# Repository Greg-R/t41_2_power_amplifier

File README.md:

# T41-2 Power Amplifier Version 1.7

This is the PCB for the Power Amplifier for the T41 "Software Defined Transceiver".
This PCB was designed using the open-source design tool Kicad 9.0.

The Power Amplifier is designed to driven by the T41-2 Low Power Amplifier, described here:

<https://github.com/Greg-R/t41_2_low_power_amplifier>

The Low Power Amplifier combined with the Power Amplifier are intended to replace the
original V11 Power Amplifier which uses IRF510 switching MOSFETs in the final amplifier
stage.  This new design will improve all aspects of power amplifier performance, 
including linearity, power, efficiency, and bandwidth.  An important difference is that
the amplifier operates from a 13.8 volt supply.  No "boost" module is required.

The schematic is here:

<https://github.com/Greg-R/t41_2_power_amplifier/blob/main/doc/t41_2_power_amplifier.pdf>

# Licensing

Please note the included license files.  The software license, GNU GENERAL PUBLIC LICENSE
Version 3, covers the design files.
The hardware license, CERN Open Hardware Licence Version 2 - Strongly Reciprocal, covers
the PCB and circuitry.

# Design Details

## Amplifier Design Notes 

The Power Amplifier is a conventional push-pull circuit using Mitsubishi RD16HHF1 devices.

The input network is an impedance matching transformer with a center-tapped secondary.
A resistive network is used for DC gate bias of the MOSFETS as well as for stability.
The two MOSFETs have independent bias adjustments due to the wide threshold voltage
variation of MOSFET devices.

A bifilar wound inductor provides DC bias to the MOSFET drains.

Each MOSFET has a transformer wound on a binocular core.  These are combined in parallel
on the output.  This results in a compact layout while preserving good bandwidth.

## DC Biasing and Thermal Protection Circuits 

A 10 volt regulator provides the bias voltage to the potentiometers which are used to set
the MOSFET quiescent bias currents.

There is also an optional "thermostat" device which shuts down the amplifier if the
temperature rises above a threshold set by a resistor value.  The thermostat is
positioned in close proximity to the output amplifier devices.  Experiments are
ongoing with this device to determine what temperature setting should be used.

Please note the electrolytic capacitors on the 13.8 volt supply net.  These are not
required in the case of a 13.8 volt supply voltage.  The 10uF ceramic capacitors, rated at
25 volts, are used in this case.  If it is desired to operate at a higher voltage, the
ceramics must be replaced with higher voltage electrolytics (not tested yet).

## Bill of Material

The Digikey BOM is here:

<https://www.digikey.com/en/mylists/list/1GX6JR00JS>

Four ferrite cores are required:

Quantity 2 BN-43-302 binocular cores.
Quantity 2 BN-43-202 binocular cores.

You will also need a small quantity of #24, #26, and #22 magnet wire.  I order this
on spools from Amazon:

<https://www.amazon.com/dp/B07DYF89T9?th=1>

I ordered the cores from:

<https://kitsandparts.com>

Also some hardware is required.  I used this outstanding heatsink:

<https://www.amazon.com/dp/B07TJY3GKP?th=1>

Some sort of stand-offs or spacers are required to hold the PCB above the heatsink.
These 5mm spacers are perfect:

<https://www.amazon.com/dp/B0CQ3TKVBD?th=1>

I use this type of caphead bolt to secure the PCB to the heatsink:

<https://www.amazon.com/dp/B0DYMYHHWH?th=1>

Two 3mm bolts and washers are required to bolt down the final amplifier devices.
A small amount of heatsink compound under the devices is recommended.

A 5 amp bladed style automotive fuse is required.

# Build Instructions

The Power Amplifier build is similar to the other boards in the T41-2 series,
with the exception being the ferrite cores which must be constructed with great
care.  I am going to create another document to cover the construction of the
three ferrite devices (T1, L2, T2 and T3).

The installation of the final amplifier devices Q1 and Q3 will be covered in
the same document as the ferrites.

The board has components on both sides.  I recommend using a hot plate for the
top side components.  Use a hot air gun for the bottom side components.

# Tune Up

## DC Bias Adjustment

There is an DC bias current adjustment for the two final amplifier MOSFETs.
The potentiometers are R17 and R11. 

It is important to set the potentiometers for minimal bias current before applying
power!!!  If the potentiometer is oriented as in the photograph (below) the 
potentiometer should be rotated counterclockwise until up against the stop.
Make sure both are set against the stop before proceeding with bias adjustment.

Since this is a Class-AB amplifier, the bias point should be set for optimal
linearity at the lowest current possible.

There is a trade-off here between linearity and efficiency.  The recommended
bias current was determined emperically.  However, if you want more efficiency,
and you are a CW operator only, decrease the bias current.  If you want even
more linearity for SSB operation, increase the bias current, with the 
trade-off being less amplifier efficiency.
 
The 13.8 volt current should be set for approximately 500 milliamperes per device
with no RF drive.  Slowly rotate one of the potentiometers clockwise until this current
is achieved.  The current may drift a few milliamperes as the devices warm up.
This is normal, and the exact bias current setting is not critical. Continue
with the second potentiometer until the total bias current is 1.0 amps. 

## Linearity Testing

The T41EEE firmware includes a "two-tone" test which can be used to evaluate the
linearity of a power amplifier.

# High Resolution Photos

The top side of the completed board:

<https://drive.google.com/file/d/1ic4hn-198JwR1nAGYp5Wp3Prv69H474b/view?usp=drive_link>

Side view of the completed module, showing the heatsink, TO-220 devices, and spacers:

<https://drive.google.com/file/d/1cEXMb9Utur-sG8AnGmGLAzppEAz-hgnM/view?usp=drive_link>

End view of the Power Amplifier, showing the spacers and heatsink:

<https://drive.google.com/file/d/1fRfvSwTNmH1s3oaT6EwBXt0dI4ggvO0P/view?usp=drive_link>

# Mounting the Power Amplifier to the T41 Radio

By drilling and tapping four holes in the extension of the heatsink, the Power
Amplifier module can be mounted to the back side of the radio. 

The FreeCad design file for a rear case panel is here:

<https://github.com/Greg-R/SDT_Case_KF5N/tree/main/case>

There are a lot of files in that folder.  The revised rear panel is:

Rear\_Full\_panel\_2025\_KF5N\_2.FCStd

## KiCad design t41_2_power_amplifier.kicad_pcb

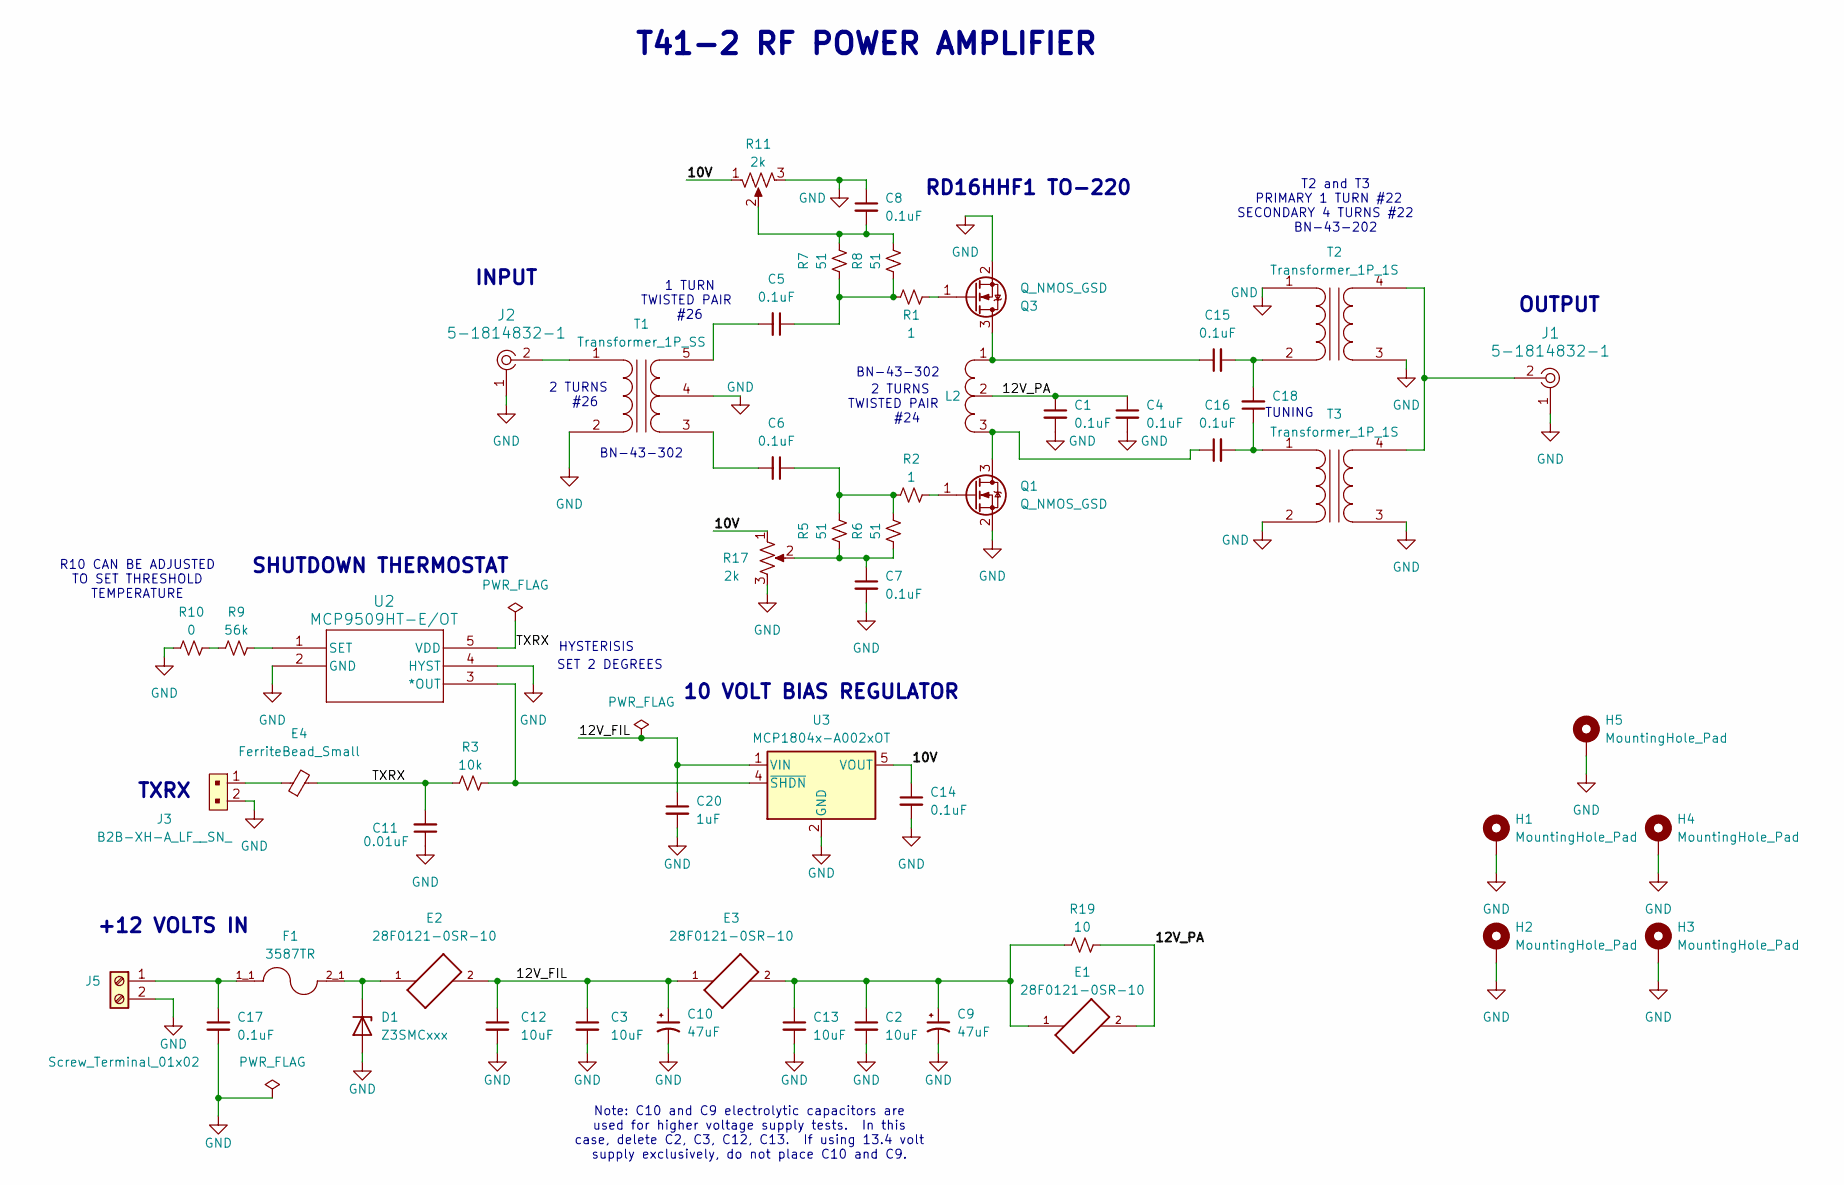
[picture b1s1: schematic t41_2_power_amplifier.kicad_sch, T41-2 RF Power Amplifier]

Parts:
C1, C4, C5, C6, C7, C8, C14, C15, C16, C17, C18: 0.1uF; C_1206_3216Metric
C2, C3, C12, C13: 10uF; C_1206_3216Metric
C9, C10: 47uF; CP_Elec_6.3x5.7
C11: 0.01uF; C_1206_3216Metric
C20: 1uF; C_1206_3216Metric
D1: Z3SMCxxx; D_SMC
E1, E2, E3: 28F0121-0SR-10; FB_28F0121-0SR-10; PARTREV J
E4: FerriteBead_Small; L_1206_3216Metric
F1: 3587TR; FUSE_3587TR; PARTREV D
H1, H2, H3, H4, H5: MountingHole_Pad; MountingHole_4.3mm_M4_DIN965_Pad
J1, J2: 5-1814832-1; RF_SMA_Vertical_5-1814832-1; MPN 5-1814832-1; Digi-Key_PN A97594-ND
J3: B2B-XH-A_LF__SN_; PinHeader_1x2_P2.5mm_Drill1.1mm; MPN B2B-XH-A(LF)(SN); Digi-Key_PN 455-2247-ND
J5: Screw_Terminal_01x02; TerminalBlock_Philmore_TB132_1x02_P5.00mm_Horizontal
L2: BN-43-202_VERTICAL
Q1, Q3: Q_NMOS_GSD; TO-220_RF_Flat_Through_Hole
R1, R2: 1; R_1206_3216Metric
R3: 10k; R_1206_3216Metric
R5, R6, R7, R8: 51; R_1206_3216Metric
R9: 56k; R_1206_3216Metric
R10: 0; R_1206_3216Metric
R11, R17: 2k; Potentiometer_Bourns_3296W_Vertical
R19: 10; R_1206_3216Metric
T1: Transformer_1P_SS; BN-43-302
T2, T3: Transformer_1P_1S; BN-43-202
U2: MCP9509HT-E/OT; SOT-23-5_MC_MCH
U3: MCP1804x-A002xOT; SOT-23-5

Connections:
/10V: C14.1, R11.1, R17.1, U3.5 (VOUT)
/12V_FIL: C3.1, C10.1, C12.1, C20.1, E2.2, E3.1, U3.1 (VIN)
/12V_PA: C1.1, C4.1, E1.2, L2.2, R19.2
/TXRX: C11.2, E4.2, R3.1, U2.5 (VDD)
GND: C1.2, C2.2, C3.2, C4.2, C7.2, C8.1, C9.2, C10.2, C11.1, C12.2, C13.2, C14.2, C17.2, C20.2, D1.2 (A), H1.1, H2.1, H3.1, H4.1, H5.1, J1.1, J2.1, J3.2, J5.2, Q1.2 (S), Q3.2 (S), R10.1, R11.3, R17.3, T1.2 (AB), T1.4 (SC), T2.1 (AA), T2.3 (SA), T3.2 (AB), T3.3 (SA), U2.2 (GND), U2.4 (HYST), U3.2 (GND)
unnamed: C5.1, R1.1, R7.1, R8.1
unnamed: C6.1, R2.1, R5.2, R6.2
unnamed: C7.1, R5.1, R6.1, R17.2
unnamed: C8.2, R7.2, R8.2, R11.2
unnamed: C2.1, C9.1, C13.1, E1.1, E3.2, R19.1
unnamed: D1.1 (K), E2.1, F1.2_1
unnamed: E4.1, J3.1
unnamed: C17.1, F1.1_1, J5.1
unnamed: C16.1, L2.3, Q1.3 (D)
unnamed: Q1.1 (G), R2.2
unnamed: C15.1, L2.1, Q3.3 (D)
unnamed: Q3.1 (G), R1.2
unnamed: R9.1, R10.2
unnamed: J2.2, T1.1 (AA)
unnamed: C6.2, T1.3 (SA)
unnamed: C5.2, T1.5 (SB)
unnamed: C15.2, C18.2, T2.2 (AB)
unnamed: J1.2, T2.4 (SB), T3.4 (SB)
unnamed: C16.2, C18.1, T3.1 (AA)
unnamed: R3.2, U2.3 (*OUT), U3.4 (~SHDN)
unnamed: R9.2, U2.1 (SET)

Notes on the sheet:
OUTPUT
BN-43-302
RD16HHF1 TO-220
SHUTDOWN THERMOSTAT
R10 CAN BE ADJUSTED TO SET THRESHOLD TEMPERATURE
Note: C10 and C9 electrolytic capacitors are used for higher voltage supply tests. In this case, delete C2, C3, C12, C13. If using 13.4 volt supply exclusively, do not place C10 and C9.
TUNING
2 TURNS #26
+12 VOLTS IN
1 TURN TWISTED PAIR #26
TXRX
T41-2 RF POWER AMPLIFIER
2 TURNS TWISTED PAIR #24
T2 and T3 PRIMARY 1 TURN #22 SECONDARY 4 TURNS #22 BN-43-202
INPUT
10 VOLT BIAS REGULATOR
HYSTERISIS
SET 2 DEGREES

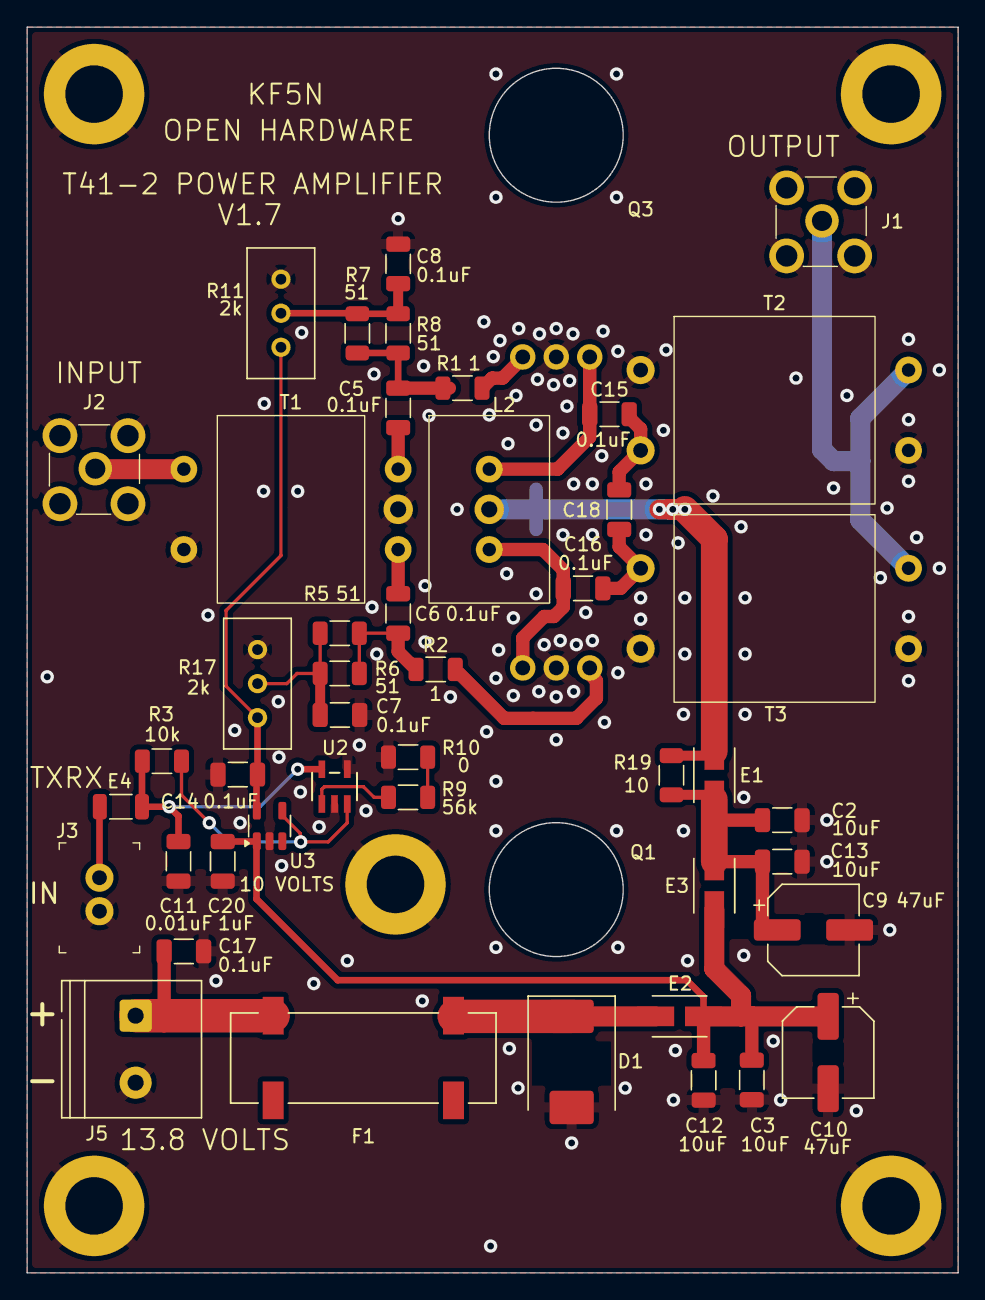
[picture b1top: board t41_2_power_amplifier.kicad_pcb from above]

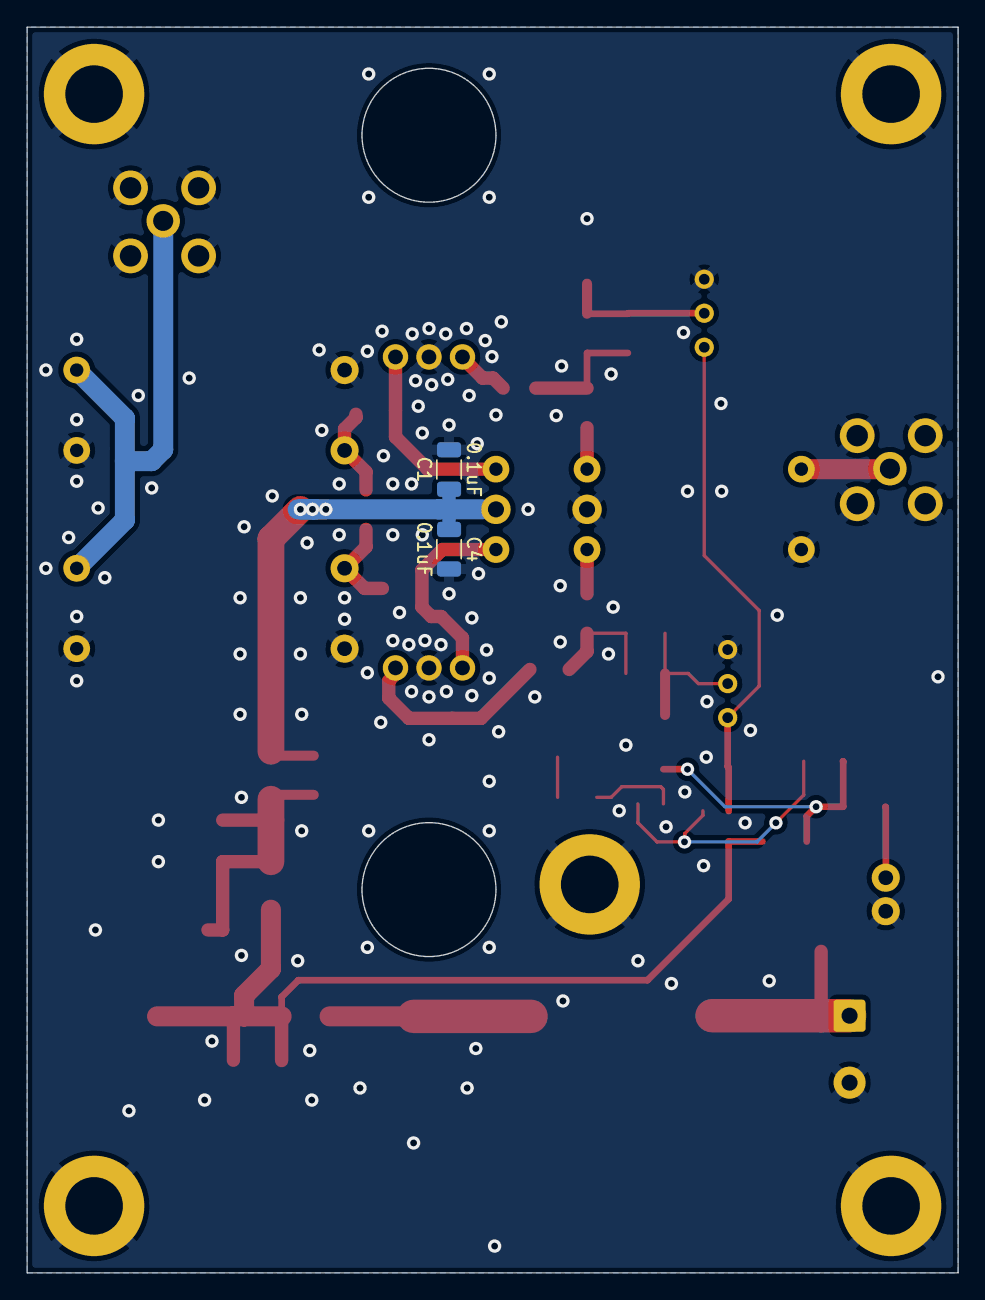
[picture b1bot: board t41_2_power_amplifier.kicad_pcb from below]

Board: 2 copper layers, 69.5 x 92.9 mm, 54 parts (2 on the bottom side), 26 nets.

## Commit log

2024-10-09 Initial commit.
2024-10-10 Schematic complete, started on layout.
2024-10-12 Branching to no-feedback experiment.
2024-10-12 Finishing PCB placement. Stopping point.
2024-10-12 Routed. Needs cleanup.
2024-10-12 Almost ready for fab.
2024-10-13 Beefed up main supply trace to final.
2024-10-13 Added another stage to the input.
2024-10-14 Release V1.0.
2024-10-24 Updated resistor values.
2024-12-01 Clean-up prior to branch.
2024-12-01 Power Amplifier module ready for fab.
2024-12-01 Ready for fab.
2024-12-22 Larger output balun design to fab.
2024-12-22 T41-2 Power Amplifier S to fab.
2024-12-23 Forgot to create zip of Gerbers.
2025-01-19 Power Amplifier to fab.
2025-01-19 Forgot to add gerbers.
2025-04-19 Added zip and archive files.
2025-04-19 Added zip files.
2025-04-23 Released to fab.
2025-04-23 Release to fab.
2025-05-04 Updated PDF schematic.
2025-05-04 Nothing but Kicad update.
2025-05-04 Added through hole TO-220 footprint.
2025-05-05 Added notes to schematic.
2025-05-21 Version V1.4 to fab.
2025-05-21 Version 1.6 first commit.
2025-05-31 Added new bypass capacitors. Added thermostat circuit.
2025-06-02 Version 1.6 to fab.
2025-06-16 Work in progress.
2025-06-22 Version 1.7, release version to fab.
2025-06-22 Added output tuning capacitor.
2025-07-05 Initial commit to Github.
2025-07-05 Cleaning up directories.
2025-07-05 Cleaning files.
2025-07-05 More clean up of initial push to Github.
2025-07-05 Cleaning up initial push to Github.
2025-07-05 Removed backup folder from repository.
2025-07-07 Added README file.
2026-05-25 Added note about supply bypass capacitors.
2026-06-28 Changed supply voltage on schematic from 12 to 13.4 volts.
